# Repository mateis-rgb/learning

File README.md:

# learning
Personnal and professionnal notes

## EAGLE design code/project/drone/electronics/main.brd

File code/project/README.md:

# Project Folder

[Introduction](./README.md)

# User Guide

- [Drone Project](drone/rapport.pdf)

# Technical Datasheets

Nothing yet.

-----------

[Contributors](./contributors.md)

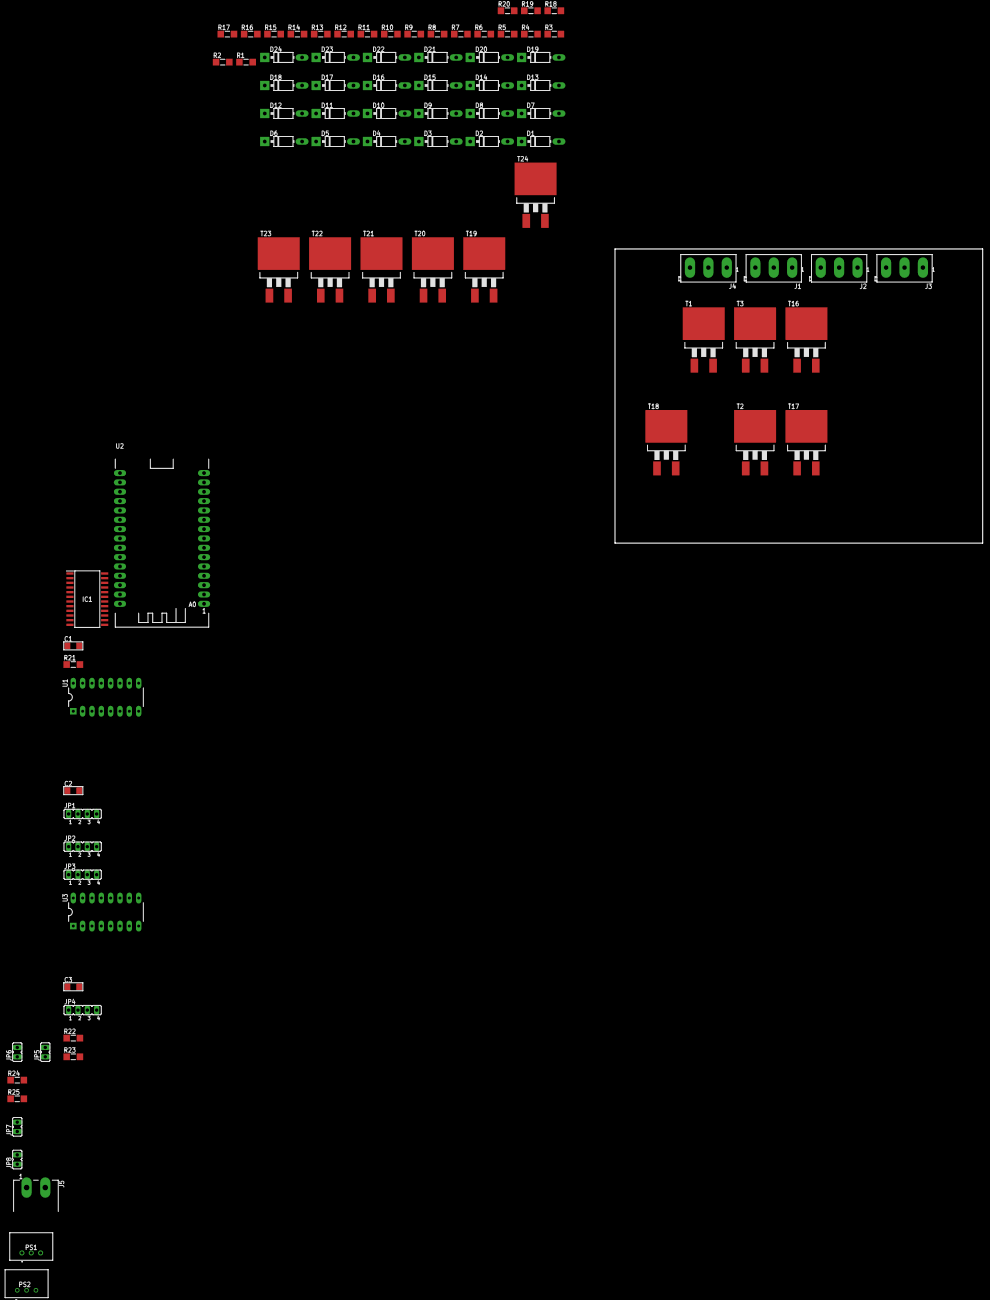
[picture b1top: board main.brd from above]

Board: 2 copper layers, 100.0 x 80.0 mm, 83 parts (0 on the bottom side), 68 nets, no tracks yet.

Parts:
C1: 0.1u; CCMS1206
C2, C3: 100n; CCMS1206
D1, D2, D3, D4, D5, D6, D7, D8, D9, D10, D11, D12, D13, D14, D15, D16, D17, D18, D19, D20, D21, D22, D23, D24: 1N4007; DO-41-10
IC1: CD74HCT4067M; SOIC127P1030X265-24N
J1, J2, J3, J4: AK500/3
J5: Batterie_IN; MSTBA2
JP1: sdCard; JP4
JP2: analog_cam; JP4
JP3: digital_cam; JP4
JP4: digital_cam_2; JP4
JP5: sd_alim; JP1
JP6: JP1
JP7: cam_alim; JP1
JP8: cam_rst_pwdn; JP1
PS1: TSR_1-2450E; TSR12450E
PS2: TSR_1-2433E; TSR-1-2433
R1, R6, R11, R16: 1M; RCMS1206
R2, R7, R12, R17: 1k; RCMS1206
R3, R4, R5, R8, R9, R10, R13, R14, R15, R18, R19, R20, R21, R24, R25: 10k; RCMS1206
R22, R23: 4.7k; RCMS1206
T1, T2, T3, T16, T17, T18, T19, T20, T21, T22, T23, T24: BTIRF3710S; D2PACK
U1, U3: 74HC595N; DIL16
U2: ESP8266-NODEMCU

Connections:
+3,3V: C1.2, C2.1, C3.1, IC1.24, JP5.1, JP7.1, JP8.1, PS2.3, R24.2, R25.2, U1.10, U1.16, U2.11, U2.16, U2.25, U3.10, U3.16
+5V: PS1.3, U2.15
+24V: J1.2, J2.2, J3.2, J4.2, J5.1, PS1.1, PS2.1, R1.2, R6.2, R11.2, R16.2
GND: C2.2, C3.2, J5.2, JP5.2, JP7.2, JP8.2, PS1.2, PS2.2, R21.1, R23.1, T1.3, T2.3, T3.3, T16.3, T17.3, T18.3, T19.3, T20.3, T21.3, T22.3, T23.3, T24.3, U1.8, U1.13, U2.10, U2.14, U2.17, U2.24, U3.8, U3.13
unnamed: D4.C, R4.1, T2.2
unnamed: D1.C, D2.C, D3.C, R1.1, R2.1
unnamed: D1.A, D4.A, R5.1, T1.1
unnamed: D2.A, D5.A, R3.2, T2.1
unnamed: D3.A, D6.A, R4.2, T3.1
unnamed: D6.C, J1.3, R3.1, T1.2
unnamed: IC1.9, R2.2
unnamed: D7.A, D10.A, R10.1, T16.1
unnamed: D5.C, J1.1, R5.2, T3.2
unnamed: D8.A, D11.A, R8.2, T17.1
unnamed: D7.C, D8.C, D9.C, R6.1, R7.1
unnamed: D9.A, D12.A, R9.2, T18.1
unnamed: D10.C, R9.1, T17.2
unnamed: D12.C, J2.3, R8.1, T16.2
unnamed: IC1.8, R7.2
unnamed: D11.C, J2.1, R10.2, T18.2
unnamed: D13.A, D16.A, R15.1, T19.1
unnamed: D14.A, D17.A, R13.2, T20.1
unnamed: D13.C, D14.C, D15.C, R11.1, R12.1
unnamed: D15.A, D18.A, R14.2, T21.1
unnamed: D16.C, R14.1, T20.2
unnamed: D18.C, J3.3, R13.1, T19.2
unnamed: IC1.7, R12.2
unnamed: D17.C, J3.1, R15.2, T21.2
unnamed: D19.A, D22.A, R20.1, T22.1
unnamed: D20.A, D23.A, R18.2, T23.1
unnamed: D19.C, D20.C, D21.C, R16.1, R17.1
unnamed: D21.A, D24.A, R19.2, T24.1
unnamed: D22.C, R19.1, T23.2
unnamed: D24.C, J4.3, R18.1, T22.2
unnamed: IC1.6, R17.2
unnamed: D23.C, J4.1, R20.2, T24.2
unnamed: JP1.1, U1.15
unnamed: JP1.2, U1.1
unnamed: JP1.3, U1.2
unnamed: JP1.4, U1.3
unnamed: IC1.13, U3.1
unnamed: C1.1, IC1.12
unnamed: IC1.14, U3.15
unnamed: IC1.11, U3.2
unnamed: IC1.10, U3.3
unnamed: IC1.1, U2.1
unnamed: IC1.15, R21.2
unnamed: U1.11, U2.30
unnamed: U1.12, U2.29
unnamed: U1.14, U2.28
unnamed: JP3.1, U1.4
unnamed: JP3.2, U1.5
unnamed: JP3.3, U1.6
unnamed: JP3.4, U1.7
unnamed: IC1.5, JP2.4
unnamed: IC1.4, JP2.3
unnamed: IC1.3, JP2.2
unnamed: IC1.2, JP2.1
unnamed: U2.27, U3.11
unnamed: U2.26, U3.12
unnamed: U2.23, U3.14
unnamed: JP4.1, U3.4
unnamed: JP4.2, U3.5
unnamed: JP4.3, U3.6
unnamed: JP4.4, R22.2
unnamed: IC1.16, JP6.1, R25.1
unnamed: R22.1, R23.2, U3.7
unnamed: IC1.17, JP6.2, R24.1

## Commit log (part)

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2023-07-13 Thèse ou essaie - Défense personnel en France
2023-09-10 1er Semaine
    Cours du 7 au 8 septembre
2023-09-10 1er Semaine
2023-09-11 replacement et ajout
2023-09-12 exos
2023-09-12 fin des exos
2023-09-12 ajout Cours base info
2023-09-12 updates files
2023-09-13 modified: code/algo-p1/tp1.cpp
2023-09-13 new file: .vscode/settings.json modified: code/algo-p1/tp1.cpp
2023-09-13 modified: .gitignore modified: code/algo-p1/tp1.cpp
2023-09-13 Nouveaux cours
2023-09-13 mise a jour des cours
2023-09-14 mise a jour
2023-09-17 cours maj
2023-09-17 maj cours
2023-09-19 maj cours + code
2023-09-30 Restructuration
2023-10-06 modified: .vscode/settings.json modified: code/algo-p1/tp1.cpp
2023-10-09 modified: code/algo-p1/ex1.cpp modified: code/algo-p1/tp1.cpp
2023-10-11 new file: code/partiels/cc1_ex1.cpp new file: code/partiels/cc1_ex2.cpp
2023-10-12 modified: code/partiels/cc1_ex2.cpp new file: code/partiels/cc1_ex3.cpp
2023-10-13 latex update
2023-10-15 cours update
2023-10-19 modified: code/partiels/cc1_ex3.cpp
2023-10-19 modified: .gitignore
2023-11-09 modified: .gitignore new file: code/algo-p2/tp/tp_2_4.cpp new file: code/algo-p2/tp/tp_2_6.cpp
2023-11-09 modified: code/algo-p2/tp/tp_2_6.cpp
2023-11-24 modified: code/algo-p2/tp/tp_2_6.cpp new file: code/partiels/cc2.cpp
2023-11-30 new file: code/algo-p2/morpion.cpp
2023-11-30 modified: code/algo-p2/morpion.cpp
2023-12-05 new file: code/paritel.cpp
2023-12-08 note de cours
2023-12-11 cours maths
2023-12-11 code update
2024-01-11 new file: code/algo-p3/tp.cpp new file: code/algo-p3/tp/fraction.cpp
2024-01-18 new file: code/test.cpp
2024-01-23 new file: code/algo-p3/tp/biblio.cpp
2024-01-25 new file: code/algo-p3/tp/fraction new file: code/algo-p3/tp/fraction.c new file: code/algo-p3/tp/tab-dyn-film.c new file: code/algo-p3/tp/tab-dyn-film.cpp
2024-02-01 new file: code/algo-p3/prep-tp.cpp new file: code/algo-p3/toto.txt
2024-02-12 new file: learning/c/lang_compare.c new file: learning/cpp/lang_compare.cpp new file: learning/lang_compare.py new file: learning/rust/lang_compare.rs
2024-02-15 modified: .gitignore modified: learning/cpp/lang_compare.cpp modified: learning/lang_compare.py
2024-02-20 new file: code/python/tp1.py new file: code/python/tp2.py
2024-02-21 new file: code/sql/tp1.sql new file: code/sql/tp2.sql
2024-02-21 new file: code/python/code_cesar.py new file: code/python/code_dico.py deleted: code/python/tp2.py
2024-02-21 renamed: code/algo-p1/.DS_Store -> code/cpp/algo-p1/.DS_Store renamed: code/algo-p1/ex1.cpp -> code/cpp/algo-p1/ex1.cpp renamed: code/algo-p1/tp1.cpp -> code/cpp/algo-p1/tp1.cpp renamed: code/algo-p2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
2024-02-21 modified: code/cpp/algo-p4/repertoire-chaine.cpp
2024-02-22 modified: code/python/code_dico.py modified: code/sql/tp2.sql new file: code/sql/tp3.sql
2024-02-27 modified: code/python/code_dico.py modified: code/python/output.txt
2024-02-28 new file: code/python/bruteforce_cesar.py modified: code/python/code_cesar.py modified: code/python/code_dico.py modified: code/python/output.txt modified: code/sql/tp3.sql new file: code/sql/tp4.sql
2024-02-29 modified: code/sql/tp2.sql modified: code/sql/tp4.sql modified: "perso/Th\303\250se ou essaie - D\303\251fense personnel en France.md"
2024-03-13 modified: code/python/bruteforce_cesar.py modified: code/python/code_cesar.py modified: code/python/input.txt modified: code/python/output.txt
2024-03-14 new file: code/sql/tp5.sql
2024-03-19 modified: README.md modified: code/python/bruteforce_cesar.py modified: code/python/input.txt
2024-03-20 new file: code/python/magic_square.py new file: code/python/magic_square.xml modified: code/sql/tp2.sql modified: code/sql/tp5.sql
2024-03-22 modified: code/python/magic_square.py
2024-03-22 modified: code/python/magic_square.py modified: code/python/magic_square.xml
2024-03-25 modified: code/python/carre_magique.py
2024-03-26 modified: .gitignore modified: code/.DS_Store modified: code/python/carre_magique.py new file: code/python/carre_magique_impair.py modified: code/python/magic_square.py deleted: code/python/magic_squ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
2024-03-27 new file: code/sql/tp6.sql
2024-03-28 modified: code/sql/tp6.sql new file: code/sql/tp8.sql
2024-03-28 modified: code/sql/tp6.sql modified: code/sql/tp8.sql
2024-03-31 py and ts comparison
2024-08-19 glouton-test
2024-09-08 folders update
2024-09-08 exos 1 lucidar.me
2024-09-08 exo 2 added
2024-09-09 add tp1
2024-09-11 modified: .zshrc modified: package-lock.json
2024-09-11 new file: add_alias.sh modified: code/c/exos_train/exo2.c modified: cours/iut/but1/c/tp1/ex4.c new file: cours/iut/but1/c/tp2/ex1.c new file: cours/iut/but1/c/tp2/ex10.c new file: cours/iut/but1/c/tp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
2024-09-17 exos update
2024-09-18 update tp2
2024-09-18 modified: cours/iut/but1/c/tp2/ex1.c modified: cours/iut/but1/c/tp2/ex10.c new file: cours/iut/but1/c/tp2/ex12.c new file: cours/iut/but1/c/tp2/ex13.c modified: cours/iut/but1/c/tp2/ex2.c modified: c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
2024-09-22 modified: add_alias.sh new file: code/c/http_request.c/main.c new file: cours/iut/but1/c/tp3/ex1.c new file: cours/iut/but1/c/tp3/ex2.c new file: cours/iut/but1/c/tp3/ex3.c new file: cours/iut/but1/c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
2024-09-22 course update
2024-09-24 modified: .vscode/settings.json modified: add_alias.sh modified: code/c/http_request.c/gui.c modified: code/c/http_request.c/main.c modified: code/c/http_request.c/request.c deleted: code/c/http_requ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
2024-09-24 http_request.c update
2024-10-06 udpate
2024-10-07 update exos
2024-10-15 webos update
2024-10-18 tp5 update
2024-10-20 add rotate 90 logic
2024-10-20 making dirs && making color rotations
2024-10-26 add bruteforce tests
2024-10-26 txt update
2024-10-27 update bruteforce comparison between py and c
2024-10-28 array lib
2024-11-02 dossier update
2024-11-02 update pdfs
2024-11-02 jpg add
2024-11-09 adding drone project
2024-11-19 renamed: code/project/drone/rapport.cls -> code/project/drone/rapport/rapport.cls renamed: code/project/drone/rapport.pdf -> code/project/drone/rapport/rapport.pdf renamed: code/project/drone/rapport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
2024-11-20 add files
2024-11-20 end of electric card
2024-11-22 new file: cours/iut/but1/sin/diagram_mini_projet.drawio
2024-11-24 update SIN
2024-12-08 add cli ts program
2024-12-27 GP update
2025-01-30 Create toto
2025-02-01 file update
2025-04-27 arb_update
2025-05-07 updatde
2025-09-11 change
2025-10-06 cours
